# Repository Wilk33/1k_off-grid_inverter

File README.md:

# Off-Grid 1kW Inverter (24V DC -> 230V AC)

> [!IMPORTANT]
> **Projekt został zamknięty i nie będzie dalej rozwijany.**
>
> Repozytorium pozostaje archiwum dotychczasowego kodu i dokumentacji. Nie są planowane kolejne etapy, poprawki ani nowe wydania.

Projekt przetwornicy off-grid o mocy 1 kW przeznaczonej do konwersji napięcia z instalacji 24V DC na napięcie sieciowe 230V AC 50Hz.
Urządzenie składa się z dwóch głównych stopni konwersji energii:

1. Przetwornica DC/DC podwyższająca napięcie z 24V do około 325V DC
2. Falownik DC/AC generujący napięcie 230V AC 50Hz

System sterowany jest przez mikrokontroler odpowiedzialny za generację sygnałów sterujących, pomiary oraz zabezpieczenia.

---

# Główne parametry

| Parametr           | Wartość        |
| ------------------ | -------------- |
| Moc znamionowa     | 1000W          |
| Napięcie wejściowe | 24V DC         |
| Napięcie pośrednie | ~325V DC       |
| Napięcie wyjściowe | 230V AC        |
| Częstotliwość      | 50Hz           |
| Typ pracy          | Off-grid       |
| Sterowanie         | Mikrokontroler |

---

# Architektura systemu

System składa się z kilku głównych bloków funkcjonalnych:

24V DC
↓
DC/DC Boost Converter
↓
325V DC Bus
↓
Full Bridge Inverter
↓
LC Filter
↓
230V AC 50Hz

Dodatkowo system zawiera:

* sterowniki bramek tranzystorów mocy
* układy pomiarowe prądu i napięcia
* system chłodzenia

---

# Moduły projektu

## 1. Przetwornica DC/DC (24V -> 325V)

Odpowiada za podwyższenie napięcia z poziomu akumulatora do napięcia magistrali DC.

Główne elementy:

* transformator wysokiej częstotliwości
* tranzystory MOSFET
* sterowniki bramek

---

## 2. Falownik (325V DC -> 230V AC)

Falownik generuje napięcie sinusoidalne poprzez modulację PWM.

Topologia:

Full Bridge (H-Bridge)

Sterowanie:

SPWM (Sinusoidal Pulse Width Modulation)

Elementy:

* tranzystory MOSFET / IGBT
* drivery bramek
* filtr LC

---

## 3. Mikrokontroler

Mikrokontroler jest centralną jednostką sterującą systemem.

Zadania:

* generowanie sygnałów PWM
* sterowanie przetwornicą DC/DC
* sterowanie falownikiem
* pomiar napięcia i prądu
* implementacja zabezpieczeń
* diagnostyka systemu

---

## 4. Sterowniki elementów mocy

Sterowniki bramek odpowiadają za szybkie i bezpieczne przełączanie tranzystorów.

Wymagania:

* izolacja galwaniczna
* odpowiedni prąd sterowania bramki
* kontrola dead-time
* ochrona przed zwarciem

---

## 5. Pomiar prądu i napięcia

Układ pomiarowy pozwala na monitorowanie parametrów pracy systemu.

Pomiar obejmuje:

* napięcie wejściowe
* napięcie magistrali DC
* napięcie wyjściowe AC
* prąd wyjściowy

Stosowane elementy:

* rezystory pomiarowe
* czujniki Halla
* dzielniki napięcia

---

## 6. Konstrukcja mechaniczna

Projekt mechaniczny obejmuje:

* obudowę
* system chłodzenia
* rozmieszczenie PCB
* radiatory dla elementów mocy

---

# Struktura repozytorium

```
hardware/ 
    dcdc_converter/
    drivers/
    inverter/
    measurements/

firmware/
    mcu_control/
    pwm_generation/
    measurements/
    protection/
```

---

# Etapy projektu

1. Projekt architektury systemu
2. Projekt przetwornicy DC/DC
3. Projekt falownika
4. Implementacja firmware mikrokontrolera
5. Projekt PCB

---

# Licencja

Projekt open hardware / open source.

---

# Autorstwo i status

Projekt był tworzony przez Codex GPT-5.6-Sol pod kierunkiem Mateusza Skipora, na podstawie jego wymagań i decyzji projektowych.

Status końcowy: projekt zamknięty, bez dalszego rozwoju.

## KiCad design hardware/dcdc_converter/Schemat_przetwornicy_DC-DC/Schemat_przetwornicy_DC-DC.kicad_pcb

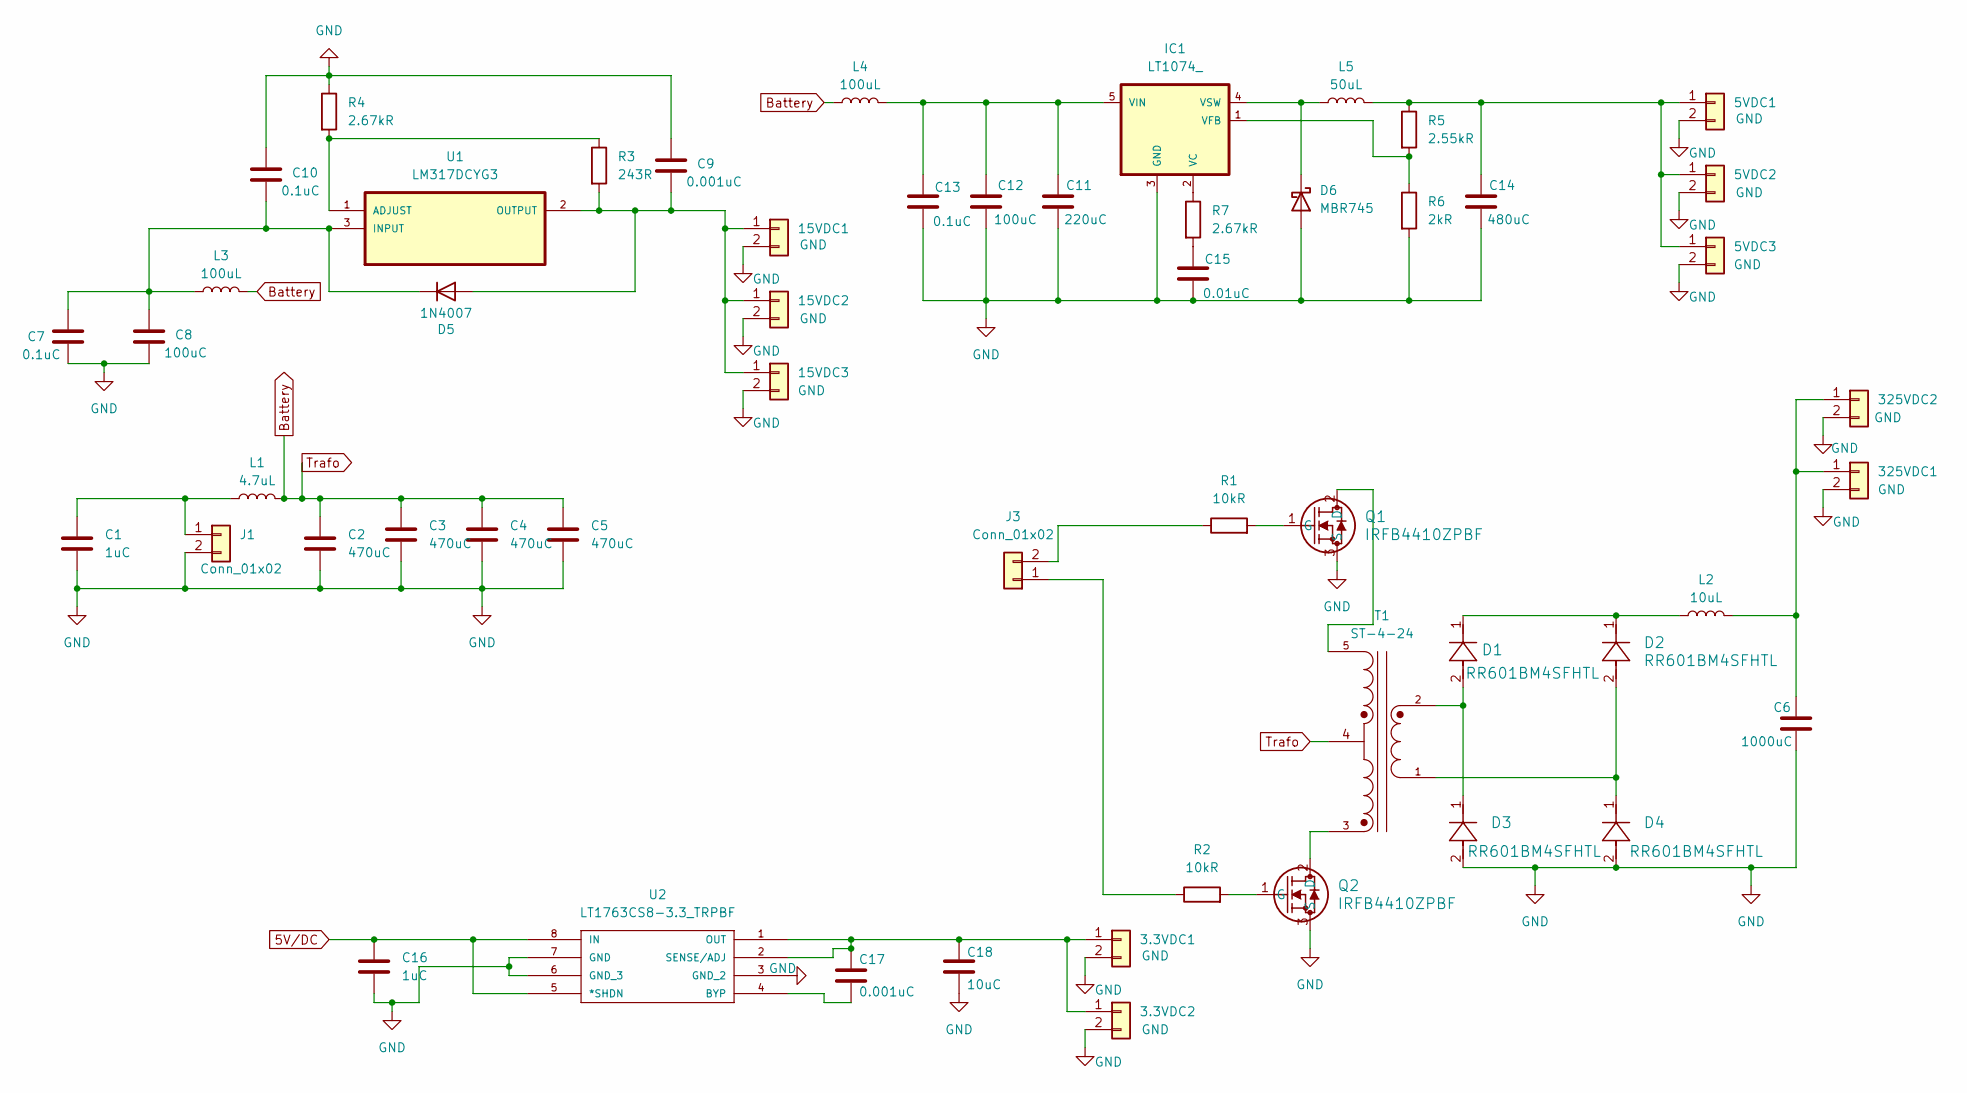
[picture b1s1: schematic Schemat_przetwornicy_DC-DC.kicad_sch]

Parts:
3.3VDC1, 3.3VDC2, 5VDC1, 5VDC2, 15VDC1, 15VDC2, 325VDC2: GND; PhoenixContact_MCV_1,5_2-G-3.5_1x02_P3.50mm_Vertical
5VDC3, 15VDC3, 325VDC1: GND; PinHeader_1x02_P2.54mm_Vertical
C1, C16: 1uC; CP_EIA-1608-08_AVX-J
C2, C3, C4, C5: 470uC; C_Radial_D16.0mm_H25.0mm_P7.50mm
C6: 1000uC; C_Radial_D16.0mm_H25.0mm_P7.50mm
C7, C10, C13: 0.1uC; CP_EIA-1608-08_AVX-J
C8, C12: 100uC; C_Radial_D16.0mm_H25.0mm_P7.50mm
C9, C17: 0.001uC; CP_EIA-1608-08_AVX-J
C11: 220uC; C_Radial_D16.0mm_H25.0mm_P7.50mm
C14: 480uC; C_Radial_D16.0mm_H25.0mm_P7.50mm
C15: 0.01uC; CP_EIA-1608-08_AVX-J
C18: 10uC; CP_EIA-1608-08_AVX-J
D1, D2, D3, D4: RR601BM4SFHTL; DIO_RR601BM4_ROM-M
D5: 1N4007; D_DO-41_SOD81_P10.16mm_Horizontal
D6: MBR745; TO-220-2_Vertical
IC1: LT1074_; TO220-5
J1: Conn_01x02; PhoenixContact_MCV_1,5_2-G-3.5_1x02_P3.50mm_Vertical
J3: Conn_01x02; PinHeader_1x02_P2.54mm_Vertical
L1: 4.7uL; L_2010_5025Metric_Pad1.52x2.65mm_HandSolder
L2: 10uL; L_2010_5025Metric_Pad1.52x2.65mm_HandSolder
L3, L4: 100uL; L_2010_5025Metric_Pad1.52x2.65mm_HandSolder
L5: 50uL; L_2010_5025Metric_Pad1.52x2.65mm_HandSolder
Q1, Q2: IRFB4410ZPBF; QNMOS1G2D3S_TO-220AB_INF
R1, R2: 10kR; R_0201_0603Metric
R3: 243R; R_0201_0603Metric
R4, R7: 2.67kR; R_0201_0603Metric
R5: 2.55kR; R_0201_0603Metric
R6: 2kR; R_0201_0603Metric
T1: ST-4-24; Transformer_Myrra_EI30-5_44000_Horizontal
U1: LM317DCYG3; SOT230P700X180-4N
U2: LT1763CS8-3.3_TRPBF; SO-8_S; MANUFACTURER_PART_NUMBER lt1763cs8

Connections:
5V/DC: C16.1, U2.5 (*SHDN), U2.8 (IN)
Battery: C2.1, C3.1, C4.1, C5.1, L1.2, L3.2, L4.1, T1.4
GND: 3.3VDC1.2, 3.3VDC2.2, 5VDC1.2, 5VDC2.2, 5VDC3.2, 15VDC1.2, 15VDC2.2, 15VDC3.2, 325VDC1.2, 325VDC2.2, C1.2, C2.2, C3.2, C4.2, C5.2, C6.2, C7.2, C8.2, C9.1, C10.1, C11.2, C12.2, C13.2, C14.2, C15.2, C16.2, C18.2, D3.2, D4.2, D6.2 (A), IC1.3 (GND), J1.2, Q1.3 (S), Q2.3 (S), R4.1, R6.2, U2.3 (GND_2), U2.6 (GND_3), U2.7 (GND); also elsewhere on the board
unnamed: 3.3VDC1.1, 3.3VDC2.1, C17.1, C18.1, U2.1 (OUT), U2.2 (SENSE/ADJ)
unnamed: 5VDC1.1, 5VDC2.1, 5VDC3.1, C14.1, L5.2, R5.1
unnamed: 15VDC1.1, 15VDC2.1, 15VDC3.1, C9.2, D5.2 (A), R3.2, U1.2 (OUTPUT), U1.4 (OUTPUT)
unnamed: 325VDC1.1, 325VDC2.1, C6.1, L2.2
unnamed: C15.1, R7.2
unnamed: D1.1, D2.1, L2.1
unnamed: D1.2, D3.1, T1.2
unnamed: D2.2, D4.1, T1.1
unnamed: C7.1, C8.1, C10.2, D5.1 (K), L3.1, U1.3 (INPUT)
unnamed: D6.1 (K), IC1.4 (VSW), L5.1
unnamed: IC1.2 (VC), R7.1
unnamed: IC1.1 (VFB), R5.2, R6.1
unnamed: C11.1, C12.1, C13.1, IC1.5 (VIN), L4.2
unnamed 16: C1.1, J1.1, L1.1; also elsewhere on the board
unnamed: J3.1, R2.1
unnamed: J3.2, R1.1
unnamed: Q1.2 (D), T1.5
unnamed: Q1.1 (G), R1.2
unnamed: Q2.2 (D), T1.3
unnamed: Q2.1 (G), R2.2
unnamed: R3.1, R4.2, U1.1 (ADJUST)
unnamed: C17.2, U2.4 (BYP)

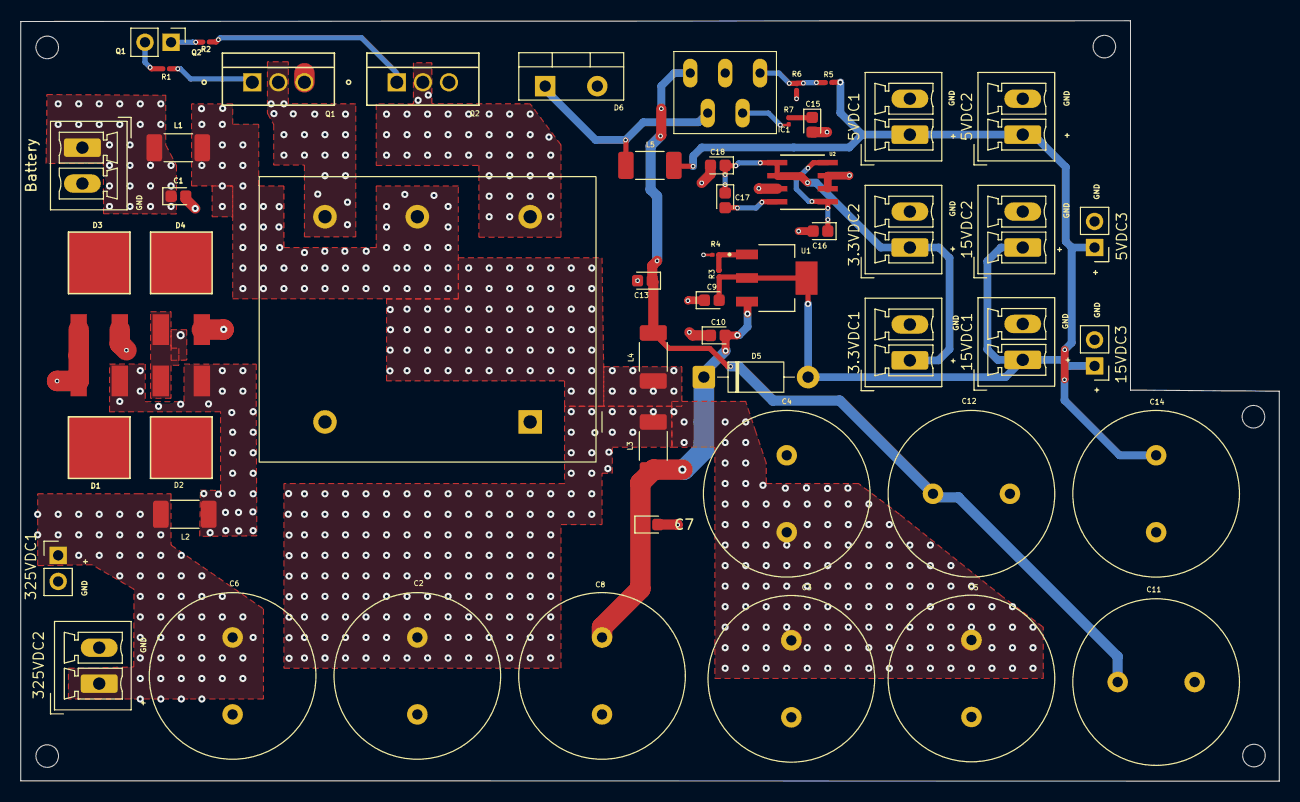
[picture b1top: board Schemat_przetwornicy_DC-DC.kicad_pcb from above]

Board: 4 copper layers, 122.7 x 74.1 mm, 54 parts (0 on the bottom side), 25 nets.

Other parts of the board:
Battery: Conn_01x02; PhoenixContact_MCV_1,5_2-G-3.5_1x02_P3.50mm_Vertical

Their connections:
GND: Battery.2; also elsewhere on the board
unnamed 16: Battery.1; also elsewhere on the board

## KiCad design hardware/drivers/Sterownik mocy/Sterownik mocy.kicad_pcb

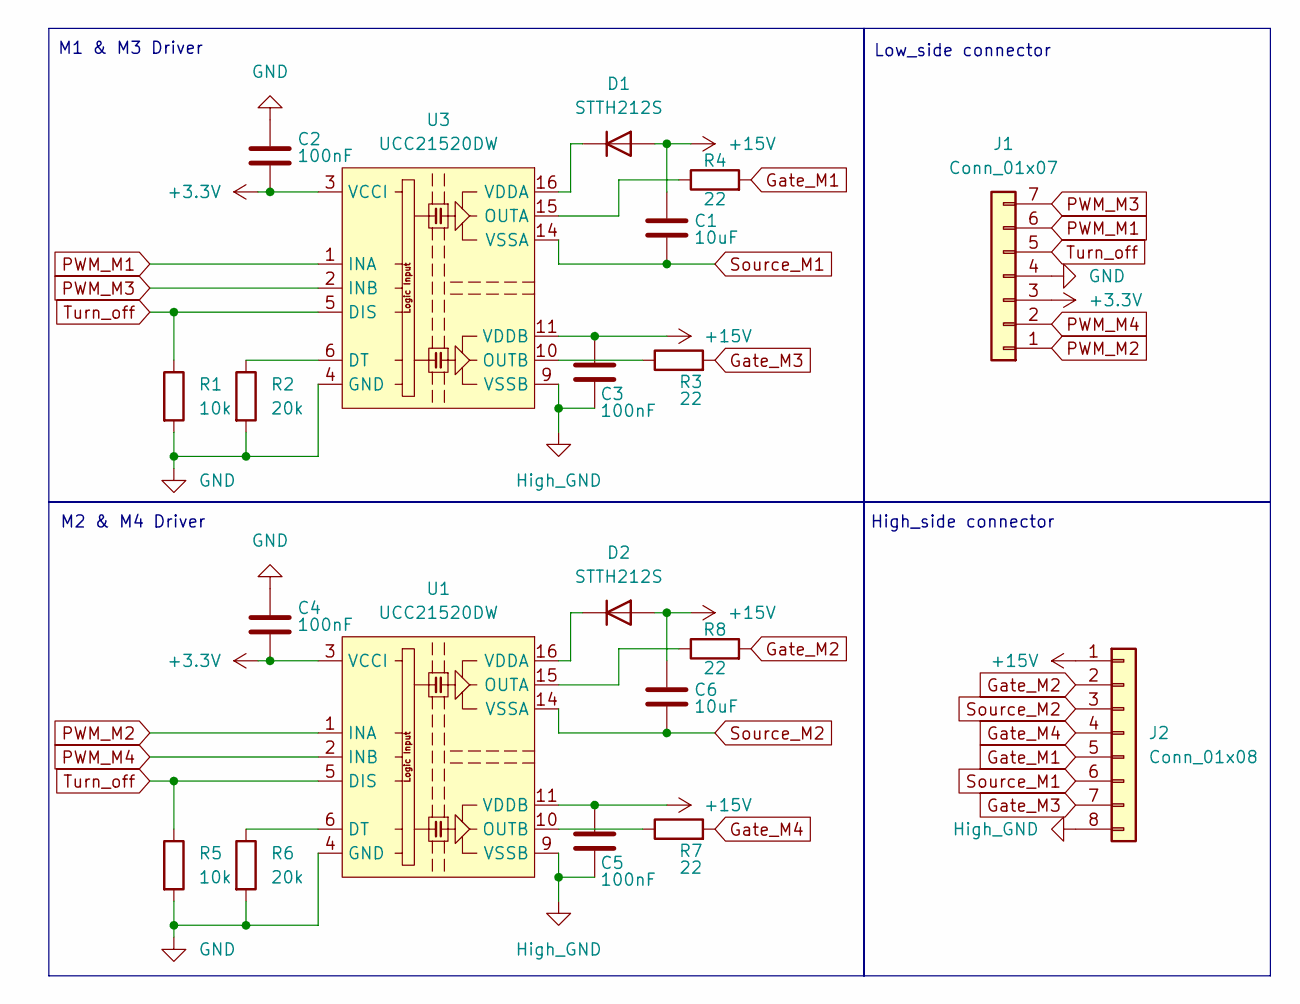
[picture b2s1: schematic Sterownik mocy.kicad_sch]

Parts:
C1, C6: 10uF; C_1206_3216Metric
C2, C3, C4, C5: 100nF; C_1206_3216Metric
D1, D2: STTH212S; D_SMC
J1: Conn_01x07; PinHeader_1x07_P1.00mm_Vertical
J2: Conn_01x08; PhoenixContact_MCV_1,5_8-G-5.08_1x08_P5.08mm_Vertical
R1, R5: 10k; R_0603_1608Metric
R2, R6: 20k; R_0603_1608Metric
R3, R4, R7, R8: 22; R_0603_1608Metric
U1, U3: UCC21520DW; SOIC-16W_7.5x10.3mm_P1.27mm

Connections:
+3.3V: C2.1, C4.1, J1.3, U1.3 (VCCI), U1.8 (VCCI), U3.3 (VCCI), U3.8 (VCCI)
+15V: C1.2, C3.2, C5.2, C6.2, D1.2 (A), D2.2 (A), J2.1, U1.11 (VDDB), U3.11 (VDDB)
GND: C2.2, C4.2, J1.4, R1.2, R2.2, R5.2, R6.2, U1.4 (GND), U3.4 (GND)
Gate_M1: J2.5, R4.2
Gate_M2: J2.2, R8.2
Gate_M3: J2.7, R3.2
Gate_M4: J2.4, R7.2
High_GND: C3.1, C5.1, J2.8, U1.9 (VSSB), U3.9 (VSSB)
unnamed: D1.1 (K), U3.16 (VDDA)
unnamed: D2.1 (K), U1.16 (VDDA)
unnamed: R6.1, U1.6 (DT)
unnamed: R8.1, U1.15 (OUTA)
unnamed: R7.1, U1.10 (OUTB)
unnamed: R2.1, U3.6 (DT)
unnamed: R4.1, U3.15 (OUTA)
unnamed: R3.1, U3.10 (OUTB)
PWM_M1: J1.6, U3.1 (INA)
PWM_M2: J1.1, U1.1 (INA)
PWM_M3: J1.7, U3.2 (INB)
PWM_M4: J1.2, U1.2 (INB)
Source_M1: C1.1, J2.6, U3.14 (VSSA)
Source_M2: C6.1, J2.3, U1.14 (VSSA)
Turn_off: J1.5, R1.1, R5.1, U1.5 (DIS), U3.5 (DIS)

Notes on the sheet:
M2 & M4 Driver
Low_side connector
High_side connector
M1 & M3 Driver

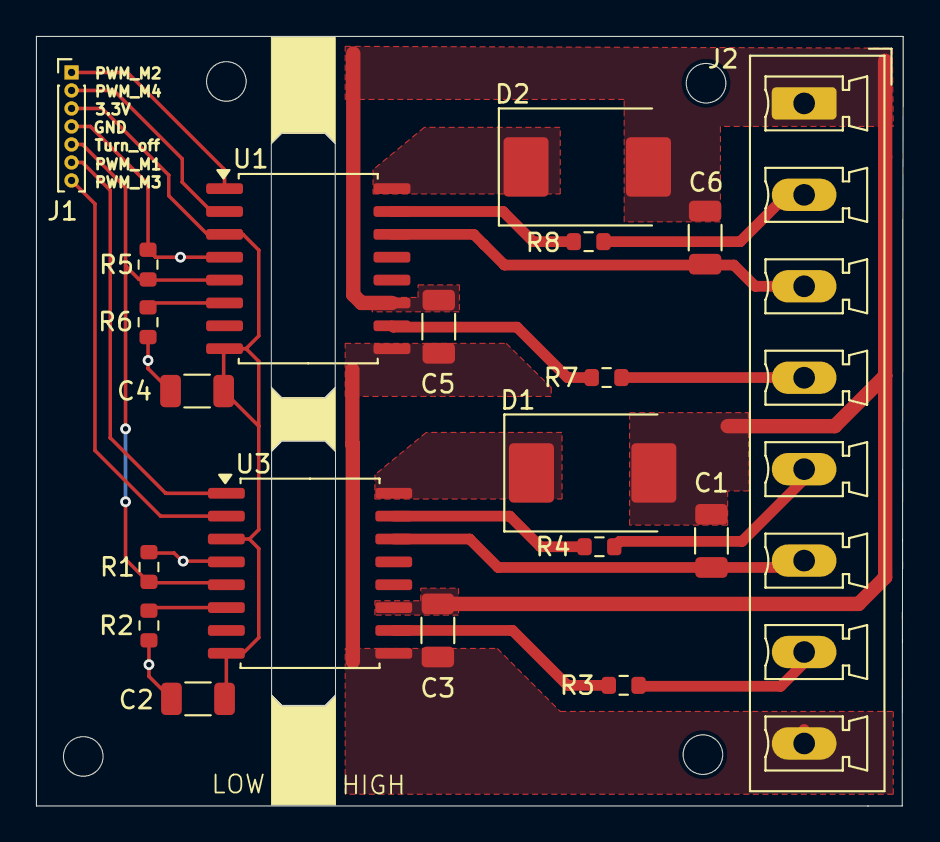
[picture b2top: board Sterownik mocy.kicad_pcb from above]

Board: 2 copper layers, 48.1 x 42.8 mm, 20 parts (0 on the bottom side), 23 nets.

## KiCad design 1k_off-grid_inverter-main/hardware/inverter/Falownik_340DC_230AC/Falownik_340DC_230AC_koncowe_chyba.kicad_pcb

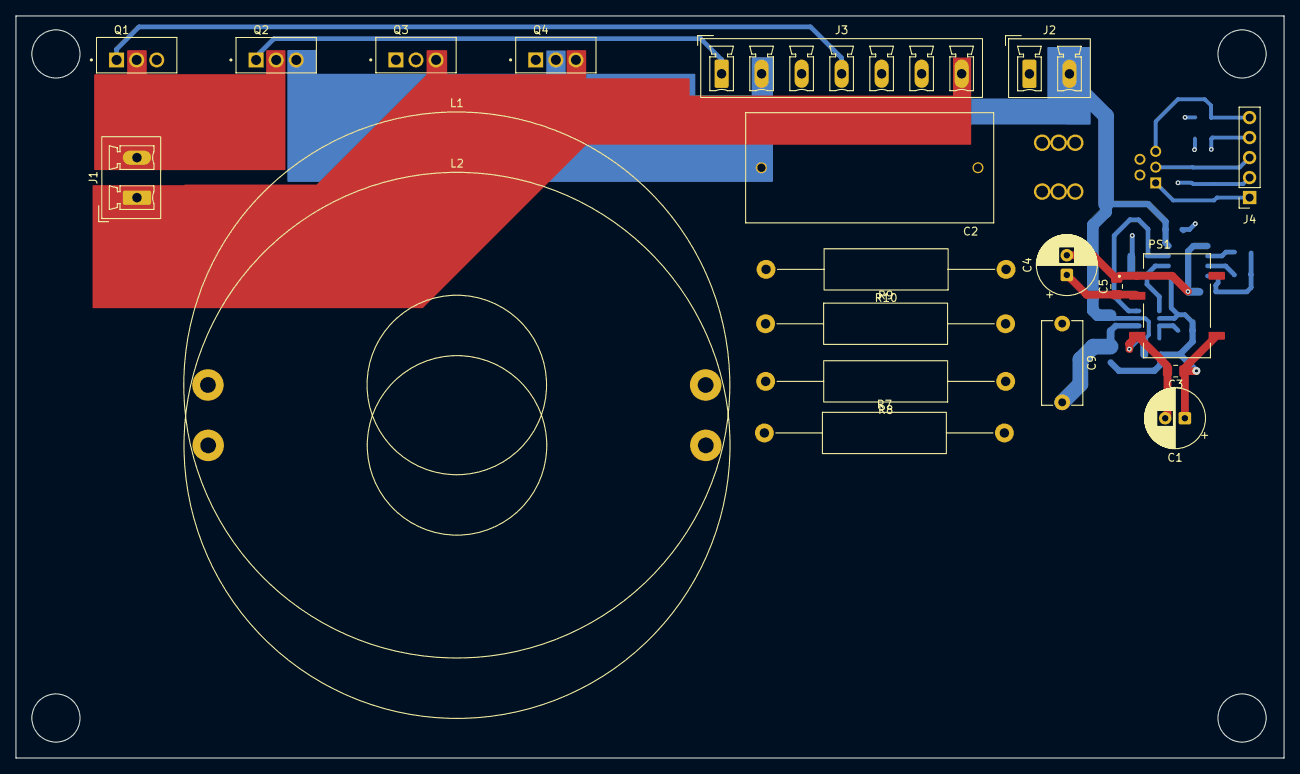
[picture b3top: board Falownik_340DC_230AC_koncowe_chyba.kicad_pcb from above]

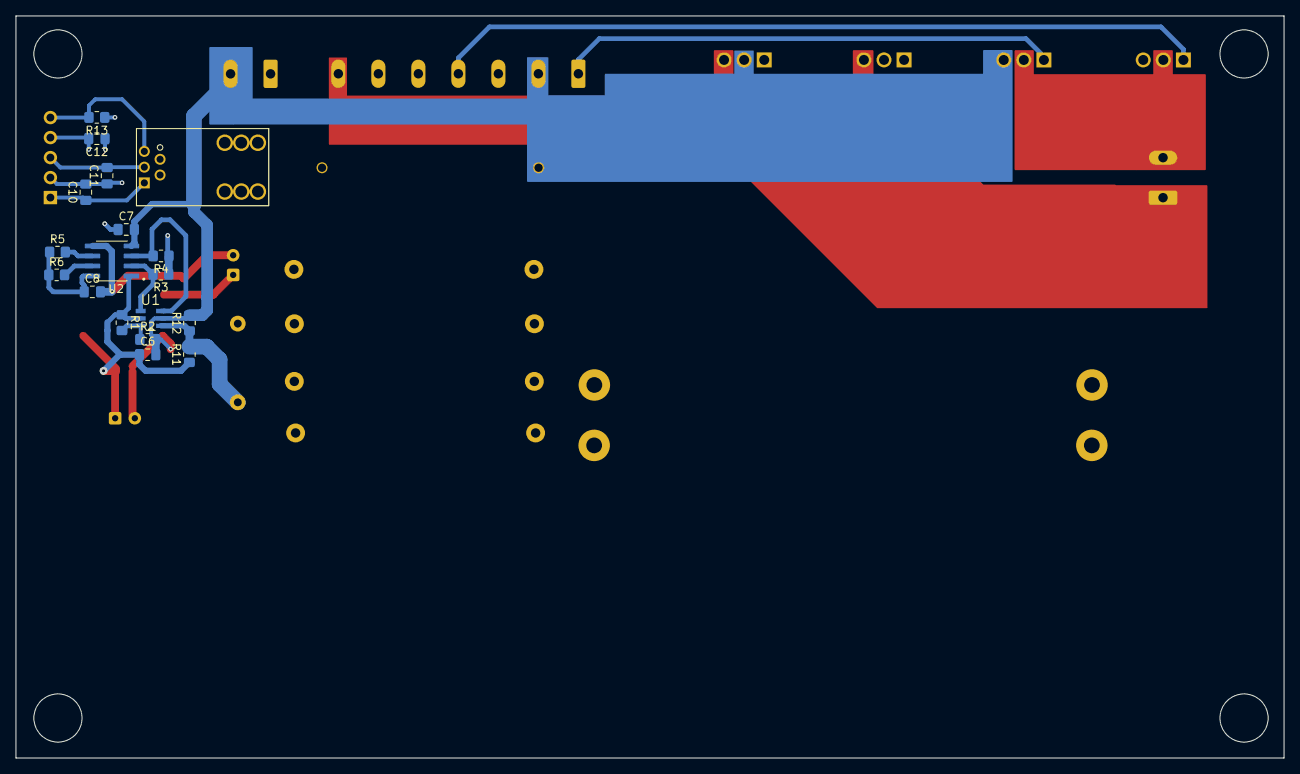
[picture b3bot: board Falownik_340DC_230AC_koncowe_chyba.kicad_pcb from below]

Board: 4 copper layers, 161.0 x 94.2 mm, 39 parts (18 on the bottom side), 28 nets.

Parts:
C1: 10u; CP_Radial_D7.5mm_P2.50mm
C2: B32674D3475K000; CAPRR2750W80L3150T1400H2450
C3, C5, C6, C7, C8, C10, C11, C12: 100n; C_0805_2012Metric_Pad1.18x1.45mm_HandSolder
C4: 4,7u; CP_Radial_D7.5mm_P2.50mm
C9: 1u; C_Disc_D10.5mm_W5.0mm_P10.00mm
J1, J2: Conn_01x02; PhoenixContact_MCV_1,5_2-G-5.08_1x02_P5.08mm_Vertical
J3: Conn_01x07; PhoenixContact_MCV_1,5_7-G-5.08_1x07_P5.08mm_Vertical
J4: Conn_01x05; PinSocket_1x05_P2.54mm_Vertical
L1, L2: 6.7mH; L_Toroid_Horizontal_D69.1mm_P63.20mm_Vishay_TJ9
PS1: PQME1-S5-S5-M; CONV_PQME1-S5-S5-M
Q1, Q2, Q3, Q4: STP7NK40Z; TO255P1020X450X1968-3B
R1, R2, R3, R4, R5, R6, R11, R12, R13: 10k; R_0805_2012Metric_Pad1.20x1.40mm_HandSolder
R7, R8, R9: 330k; R_Axial_DIN0516_L15.5mm_D5.0mm_P30.48mm_Horizontal
R10: 4,7k; R_Axial_DIN0516_L15.5mm_D5.0mm_P30.48mm_Horizontal
U1: MCP3421A1T-E_CH; SOT95P280X145-6N
U2: ISO1540DR; SOIC127P599X175-8N
U3: HO10-P; current_sensor

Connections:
0V: C10.2, C11.1, C12.1, J4.2, U3.2 (0V)
+3.3V: C8.1, R5.1, R6.1, U2.8 (VCC2)
+5V: C4.1, C5.1, PS1.2 (VIN)
+5VA: C1.1, C3.1, C6.1, C7.1, PS1.5 (+VOUT), R1.1, R3.1, R4.1, R11.1, U1.5 (VDD), U2.1 (VCC1)
AC_1: J3.5, L1.1, L2.1, Q1.3, Q3.2
AC_2: C1.2, C2.2, C3.2, C6.2, C7.2, J2.2, J3.2, PS1.4 (0V), Q2.3, Q4.2, R2.2, R10.2, R12.2, U1.2 (VSS), U2.4 (GND1)
AC_Out_1: C2.1, L1.2, L2.2, R7.1, U3.6 (IP_A), U3.7 (IP_B), U3.8 (IP_C)
AC_WYJ: J2.1, U3.9 (IP_A), U3.10 (IP_B), U3.11 (IP_C)
ADC1: C9.2, R11.2, R12.1, U1.1 (VIN+)
DC_+: J1.2, Q1.2, Q2.2
DC_-: J1.1, J3.7, Q3.3, Q4.3
GND: C4.2, C5.2, C8.2, PS1.1 (GND), U2.5 (GND2)
Gate_M1: J3.4, Q1.1
Gate_M2: J3.1, Q2.1
Gate_M3: J3.6, Q3.1
Gate_M4: J3.3, Q4.1
unnamed: C9.1, R9.2, R10.1
unnamed: R7.2, R8.1
unnamed: R8.2, R9.1
unnamed: R1.2, R2.1, U1.6 (VIN-)
OCD: J4.5, R13.2, U3.5 (OCD)
SCLA: R4.2, U1.3 (SCL), U2.3 (SCL1)
SCL/2: R5.2, U2.6 (SCL2)
SDAA: R3.2, U1.4 (SDA), U2.2 (SDA1)
SDA/2: R6.2, U2.7 (SDA2)
U+: C10.1, J4.1, R13.1, U3.1 (+Uc)
VOUT: C11.2, J4.3, U3.3 (Vout)
VREF: C12.2, J4.4, U3.4 (Vref)

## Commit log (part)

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2026-03-05 Add initial README for 1kW off-grid inverter project
2026-03-05 hardware
2026-03-05 README hardware
2026-03-05 Add firmware directory structure
2026-03-05 README firmware
2026-03-30 Add files via upload
    Schemat falownika (brak PCB)
2026-04-21 Dodane wymiary sterownika
2026-05-25 Replace inverter zip with extracted files
2026-05-26 Add measurement files
2026-05-29 Aktualizacja projektu
2026-06-02 Update ESP32 firmware and clean ignored files
